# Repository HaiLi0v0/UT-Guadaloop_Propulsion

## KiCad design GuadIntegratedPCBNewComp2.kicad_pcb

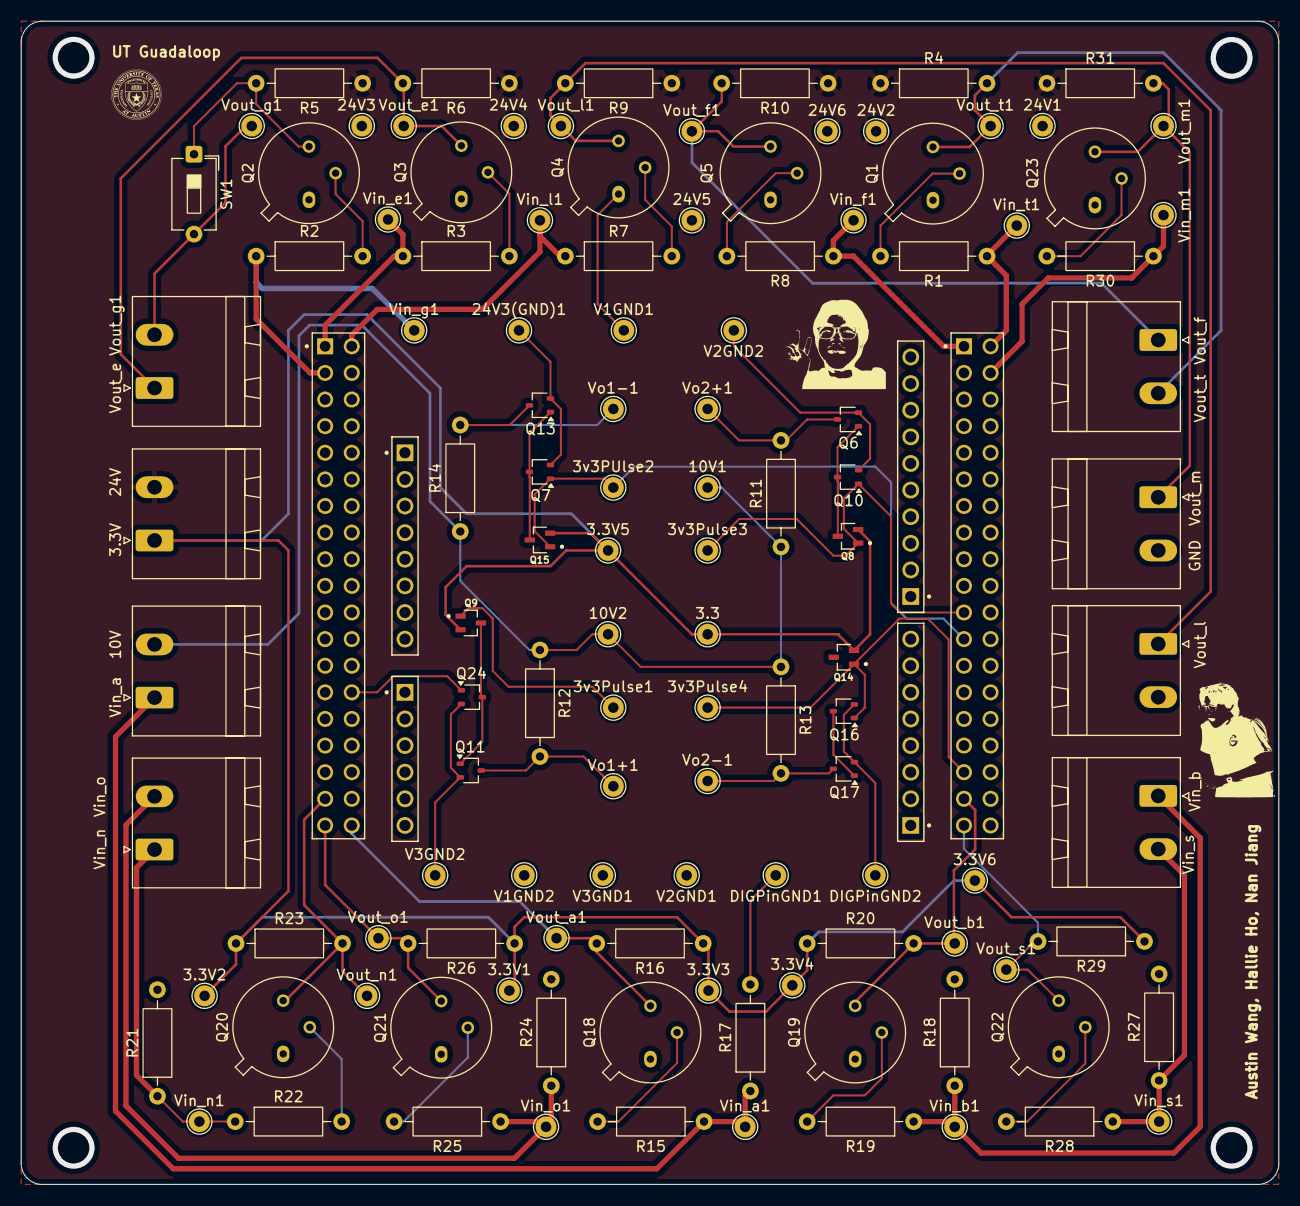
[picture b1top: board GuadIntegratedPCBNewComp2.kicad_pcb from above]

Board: 2 copper layers, 120.0 x 111.0 mm, 118 parts (0 on the bottom side), 50 nets.

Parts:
3.3, 3.3V5: V1 = 3.3; TestPoint_THTPad_D2.0mm_Drill1.0mm
3.3V1, 3.3V2, 3.3V3, 3.3V4, 3.3V6, 24V1, 24V2, 24V3, 24V4, 24V5, 24V6: Vs; TestPoint_THTPad_D2.0mm_Drill1.0mm
3v3PUlse2, 3v3Pulse4: V3 = 3.3 PULSE; TestPoint_THTPad_D2.0mm_Drill1.0mm
3v3Pulse1, 3v3Pulse3: V4 = 3.3 Pulse; TestPoint_THTPad_D2.0mm_Drill1.0mm
10V1, 10V2: V2 = 10 V; TestPoint_THTPad_D2.0mm_Drill1.0mm
24V3(GND)1: Vs GND; TestPoint_THTPad_D2.0mm_Drill1.0mm
DIGPinGND1, DIGPinGND2: V4 GND; TestPoint_THTPad_D2.0mm_Drill1.0mm
J2: Screw_Terminal_01x02; PhoenixContact_MSTBA_2,5_2-G-5,08_1x02_P5.08mm_Horizontal
Q1, Q2, Q3, Q4, Q5, Q18, Q19, Q20, Q21, Q22, Q23: 2N2219; TO-39-3
Q6, Q7, Q10, Q11, Q13, Q16, Q17, Q24: BSS214NW; SOT-323_SC-70
Q8, Q9, Q14, Q15: BSS209PW_H6327; SOT65P210X100-3N
R1, R2, R3, R7, R8, R15, R19, R22, R25, R28, R30: 25k; R_Axial_DIN0207_L6.3mm_D2.5mm_P10.16mm_Horizontal
R4, R5, R6, R9, R10, R11, R12, R13, R14, R16, R20, R23, R26, R29, R31: 1200; R_Axial_DIN0207_L6.3mm_D2.5mm_P10.16mm_Horizontal
R17, R18, R21, R24, R27: 100k; R_Axial_DIN0207_L6.3mm_D2.5mm_P10.16mm_Horizontal
SW1: SW_SPST; SW_DIP_SPSTx01_Slide_6.7x4.1mm_W7.62mm_P2.54mm_LowProfile
U1: NUCLEO-F446RE; MODULE_NUCLEO-F446RE
V1GND1, V1GND2: V1 GND; TestPoint_THTPad_D2.0mm_Drill1.0mm
V2GND1, V2GND2: V2 GND; TestPoint_THTPad_D2.0mm_Drill1.0mm
V3GND1, V3GND2: V3 GND; TestPoint_THTPad_D2.0mm_Drill1.0mm
Vin_a: Screw_Terminal_01x02; PhoenixContact_MSTBA_2,5_2-G-5,08_1x02_P5.08mm_Horizontal
Vin_a1: 24V; TestPoint_THTPad_D2.0mm_Drill1.0mm
Vin_b: Screw_Terminal_01x02; PhoenixContact_MSTBA_2,5_2-G-5,08_1x02_P5.08mm_Horizontal
Vin_b1: 5V; TestPoint_THTPad_D2.0mm_Drill1.0mm
Vin_e1: 5V; TestPoint_THTPad_D2.0mm_Drill1.0mm
Vin_f1: 5V; TestPoint_THTPad_D2.0mm_Drill1.0mm
Vin_g1: Vs; TestPoint_THTPad_D2.0mm_Drill1.0mm
Vin_l1: 5V; TestPoint_THTPad_D2.0mm_Drill1.0mm
Vin_m1: 5V; TestPoint_THTPad_D2.0mm_Drill1.0mm
Vin_n: Screw_Terminal_01x02; PhoenixContact_MSTBA_2,5_2-G-5,08_1x02_P5.08mm_Horizontal
Vin_n1: 5V; TestPoint_THTPad_D2.0mm_Drill1.0mm
Vin_o1: 5V; TestPoint_THTPad_D2.0mm_Drill1.0mm
Vin_s1: 5V; TestPoint_THTPad_D2.0mm_Drill1.0mm
Vin_t1: Vs; TestPoint_THTPad_D2.0mm_Drill1.0mm
Vo1+1, Vo1-1, Vo2+1, Vo2-1: Vo; TestPoint_THTPad_D2.0mm_Drill1.0mm
Vout_a1: Vs; TestPoint_THTPad_D2.0mm_Drill1.0mm
Vout_b1: Vs; TestPoint_THTPad_D2.0mm_Drill1.0mm
Vout_e1: Vs; TestPoint_THTPad_D2.0mm_Drill1.0mm
Vout_f1: Vs; TestPoint_THTPad_D2.0mm_Drill1.0mm
Vout_g1: Screw_Terminal_01x02; PhoenixContact_MSTBA_2,5_2-G-5,08_1x02_P5.08mm_Horizontal
Vout_g1#2: Vs; TestPoint_THTPad_D2.0mm_Drill1.0mm
Vout_l: Screw_Terminal_01x02; PhoenixContact_MSTBA_2,5_2-G-5,08_1x02_P5.08mm_Horizontal
Vout_l1: Vs; TestPoint_THTPad_D2.0mm_Drill1.0mm
Vout_m: Screw_Terminal_01x02; PhoenixContact_MSTBA_2,5_2-G-5,08_1x02_P5.08mm_Horizontal
Vout_m1: Vs; TestPoint_THTPad_D2.0mm_Drill1.0mm
Vout_n1: Vs; TestPoint_THTPad_D2.0mm_Drill1.0mm
Vout_o1: Vs; TestPoint_THTPad_D2.0mm_Drill1.0mm
Vout_s1: Vs; TestPoint_THTPad_D2.0mm_Drill1.0mm
Vout_t: Screw_Terminal_01x02; PhoenixContact_MSTBA_2,5_2-G-5,08_1x02_P5.08mm_Horizontal
Vout_t1: Vs; TestPoint_THTPad_D2.0mm_Drill1.0mm

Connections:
3.3V: 3.3.1, 3.3V1.1, 3.3V2.1, 3.3V3.1, 3.3V4.1, 3.3V5.1, 3.3V6.1, J2.1, Q8.2 (S), Q9.2 (S), Q14.2 (S), Q15.2 (S), R16.1, R20.1, R23.1, R26.1, R29.1
3v3Pulse1: 3v3Pulse1.1, Q9.1 (G), Q24.1 (G), U1.CN7_28 (PA0)
3v3Pulse2: 3v3PUlse2.1, Q7.1 (G), Q15.1 (G), U1.CN10_23 (PA8)
3v3Pulse3: 3v3Pulse3.1, Q8.1 (G), Q10.1 (G), U1.CN10_21 (PA9)
3v3Pulse4: 3v3Pulse4.1, Q14.1 (G), Q16.1 (G), U1.CN10_33 (PA10)
10v: 10V1.1, 10V2.1, R11.1, R12.1, R13.1, R14.1, Vin_a.2
24v: 24V1.1, 24V2.1, 24V3.1, 24V4.1, 24V5.1, 24V6.1, J2.2, R4.1, R5.1, R6.1, R9.1, R10.1, R31.1
GND: 24V3(GND)1.1, DIGPinGND1.1, DIGPinGND2.1, Q1.1 (E), Q2.1 (E), Q3.1 (E), Q4.1 (E), Q5.1 (E), Q6.2 (S), Q7.2 (S), Q10.2 (S), Q11.2 (S), Q13.2 (S), Q16.2 (S), Q17.2 (S), Q18.1 (E), Q19.1 (E), Q20.1 (E), Q21.1 (E), Q22.1 (E), Q23.1 (E), Q24.2 (S), R17.2, R18.2, R21.2, R24.2, R27.2, V1GND1.1, V1GND2.1, V2GND1.1, V2GND2.1, V3GND1.1, V3GND2.1, Vout_m.2
unnamed: Q1.2 (B), R1.2
unnamed: Q2.2 (B), R2.2
unnamed: Q2.3 (C), R5.2, SW1.1 (A)
unnamed: Q3.2 (B), R3.2
unnamed: Q4.2 (B), R7.2
unnamed: Q5.2 (B), R8.2
unnamed: Q6.3 (D), R11.2, Vo2+1.1
unnamed: Q6.1 (G), Q8.3 (D), Q10.3 (D)
unnamed: Q11.3 (D), R12.2, Vo1+1.1
unnamed: Q9.3 (D), Q11.1 (G), Q24.3 (D)
unnamed: Q13.3 (D), R14.2, Vo1-1.1
unnamed: Q7.3 (D), Q13.1 (G), Q15.3 (D)
unnamed: Q14.3 (D), Q16.3 (D), Q17.1 (G)
unnamed: Q17.3 (D), R13.2, Vo2-1.1
unnamed: Q18.2 (B), R15.2
unnamed: Q19.2 (B), R19.2
unnamed: Q20.2 (B), R22.2
unnamed: Q21.2 (B), R25.2
unnamed: Q22.2 (B), R28.2
unnamed: Q23.2 (B), R30.2
Vin_a: R15.1, R17.1, Vin_a.1, Vin_a1.1
Vin_b: R18.1, R19.1, Vin_b.1, Vin_b1.1
Vin_e: R3.1, U1.CN7_1 (PC10), Vin_e1.1
Vin_f: R8.1, U1.CN10_1 (PC9), Vin_f1.1
Vin_g1: R2.1, U1.CN7_3 (PC12), Vin_g1.1
Vin_l: R7.1, U1.CN7_2 (PC11), Vin_l1.1
Vin_m: R30.1, U1.CN10_4 (PC6), Vin_m1.1
Vin_n: R21.1, R22.1, Vin_n.1, Vin_n1.1
Vin_o: R24.1, R25.1, Vin_n.2, Vin_o1.1
Vin_s: R27.1, R28.1, Vin_b.2, Vin_s1.1
Vin_t1: R1.1, U1.CN10_2 (PC8), Vin_t1.1
Vout_a: Q18.3 (C), R16.2, U1.CN7_38 (PC0/PB8), Vout_a1.1
Vout_b: Q19.3 (C), R20.2, U1.CN10_35 (PA2), Vout_b1.1
Vout_e: Q3.3 (C), R6.2, Vout_e1.1, Vout_g1.1
Vout_f: Q5.3 (C), R10.2, Vout_f1.1, Vout_t.1
Vout_g1: SW1.2 (B), Vout_g1.2, Vout_g1#2.1
Vout_l: Q4.3 (C), R9.2, Vout_l.1, Vout_l1.1
Vout_m: Q23.3 (C), R31.2, Vout_m.1, Vout_m1.1
Vout_n: Q20.3 (C), R23.2, U1.CN7_35 (PC2), Vout_n1.1
Vout_o: Q21.3 (C), R26.2, U1.CN7_37 (PC3), Vout_o1.1
Vout_s: Q22.3 (C), R29.2, U1.CN10_37 (PA3), Vout_s1.1
Vout_t1: Q1.3 (C), R4.2, Vout_t.2, Vout_t1.1
